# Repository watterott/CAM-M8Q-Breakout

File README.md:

# CAM-M8Q-Breakout
Breakout with u-blox CAM-M8Q Multi GNSS Module.

* [u-blox CAM-M8Q](https://www.u-blox.com/de/product/cam-m8-series) Multi GNSS Module
* GNSS Systems: GPS/QZSS, Galileo, GLONASS, BeiDou
* Interfaces: UART (default 9600 8N1), I2C/TWI (address 0x42), SPI
* on-board Antenna and optional external Antenna (u.Fl)
* 2.7 - 3.6V Power Supply
* Open-Source and released under the [Creative Commons Attribution Share-Alike License](https://creativecommons.org/licenses/by-sa/4.0/).
* **[Documentation on learn.watterott.com](https://learn.watterott.com)**

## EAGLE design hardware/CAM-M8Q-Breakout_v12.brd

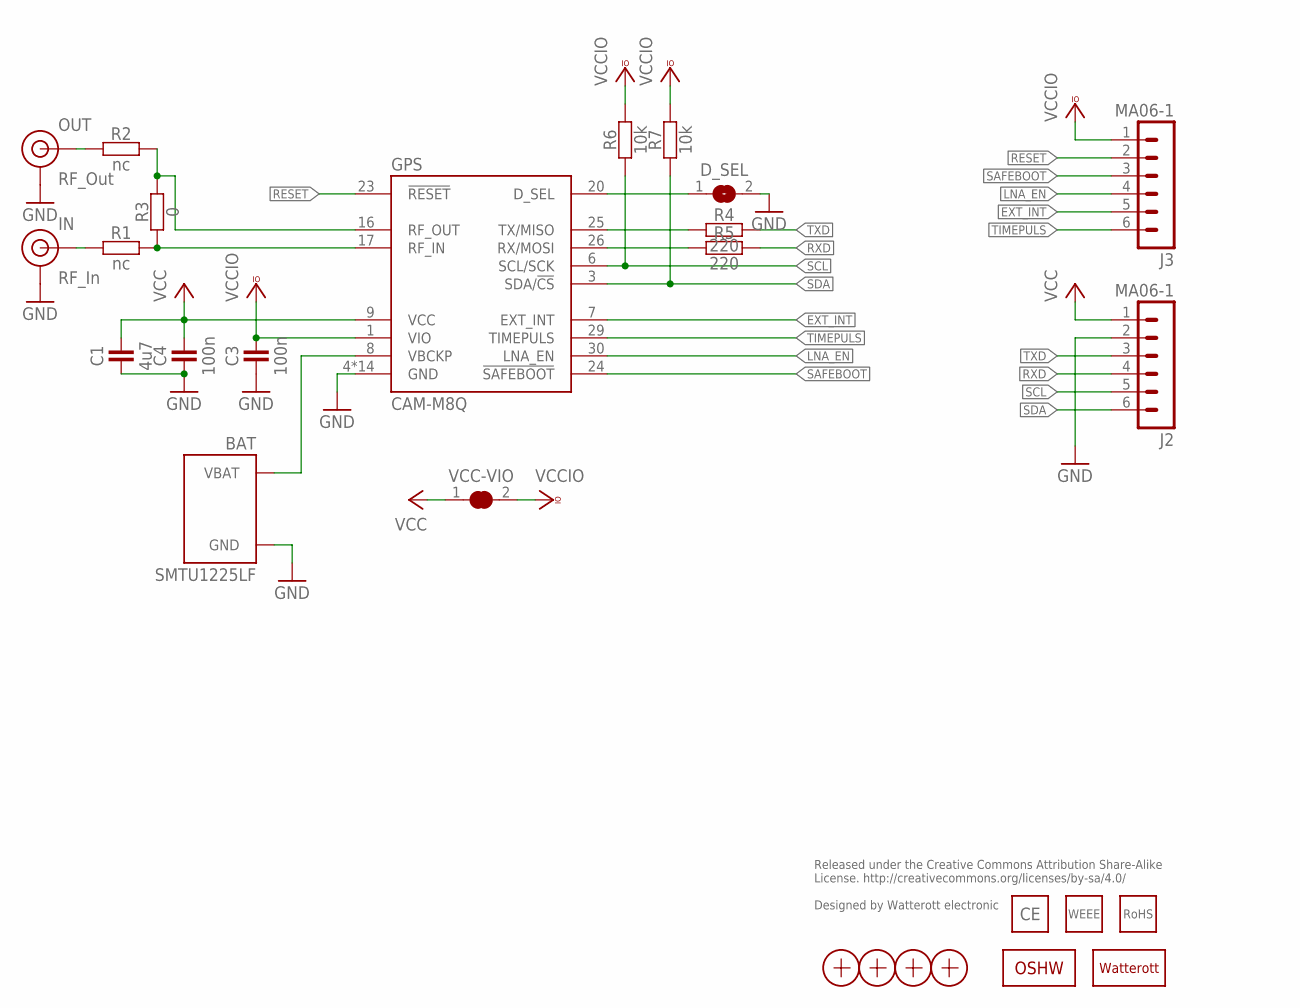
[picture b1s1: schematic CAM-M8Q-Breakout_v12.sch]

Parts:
BAT: SMTU1225LF; BAT-SMTU1225LF
C1: 4u7; C0402
C3, C4: 100n; C0402
D_SEL: JUMPER2-0603-NC; JUMPER2-0603_NC
GPS: CAM-M8Q
IN: RF_In; U.FL
J2, J3: MA06-1
LOGO1: LOGO-S_PLACE_M; SPARK_TPLACE_M
LOGO2: OSHW_LOGOX0070; OSHW_6X70
LOGO3: LOGO_CE-2; CE_2MM
LOGO4: LOGO_WEEE-4; WEEE_4MM
LOGO5: LOGO_ROHS-2; ROHS_2MM
OUT: RF_Out; U.FL
R1, R2: nc; C0402
R3: 0; C0402
R4, R5: 220; C0402
R6, R7: 10k; C0402
VCC-VIO: JUMPER2-0603-NC; JUMPER2-0603_NC
X1, X2, X3, X4: PASSER-07; PASSER_07MM

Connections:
D_SEL: D_SEL.1, GPS.20 (D_SEL)
EXT_INT: GPS.7 (EXT_INT), J3.5
GND: BAT.- (GND), C1.1, C3.1, C4.1, D_SEL.2, GPS.4 (GND), GPS.5 (GND), GPS.10 (GND), GPS.11 (GND), GPS.12 (GND), GPS.13 (GND), GPS.14 (GND), GPS.15 (GND), GPS.18 (GND), GPS.19 (GND), GPS.21 (GND), GPS.22 (GND), GPS.27 (GND), GPS.31 (GND), IN.1 (GND), IN.2 (GND), J2.2, OUT.1 (GND), OUT.2 (GND)
IN: IN.FEED (SIGNAL), R1.1
LNA_EN: GPS.30 (LNA_EN), J3.4
unnamed: GPS.25 (TX/MISO), R4.1
unnamed: GPS.26 (RX/MOSI), R5.1
OUT: OUT.FEED (SIGNAL), R2.1
RESET: GPS.23 (!RESET), J3.2
RFIN: GPS.17 (RF_IN), R1.2, R3.1
RFOUT: GPS.16 (RF_OUT), R2.2, R3.2
RXD: J2.4, R5.2
SAFEBOOT: GPS.24 (!SAFEBOOT), J3.3
SCL: GPS.6 (SCL/SCK), J2.5, R6.1
SDA: GPS.3 (SDA/!CS), J2.6, R7.1
TIMEPULS: GPS.29 (TIMEPULS), J3.6
TXD: J2.3, R4.2
VBCKP: BAT.+ (VBAT), GPS.8 (VBCKP)
VCC: C1.2, C4.2, GPS.9 (VCC), J2.1, VCC-VIO.1
VCCIO: C3.2, GPS.1 (VIO), J3.1, R6.2, R7.2, VCC-VIO.2

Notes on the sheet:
Released under the Creative Commons Attribution Share-Alike License. http://creativecommons.org/licenses/by-sa/4.0/ Designed by Watterott electronic

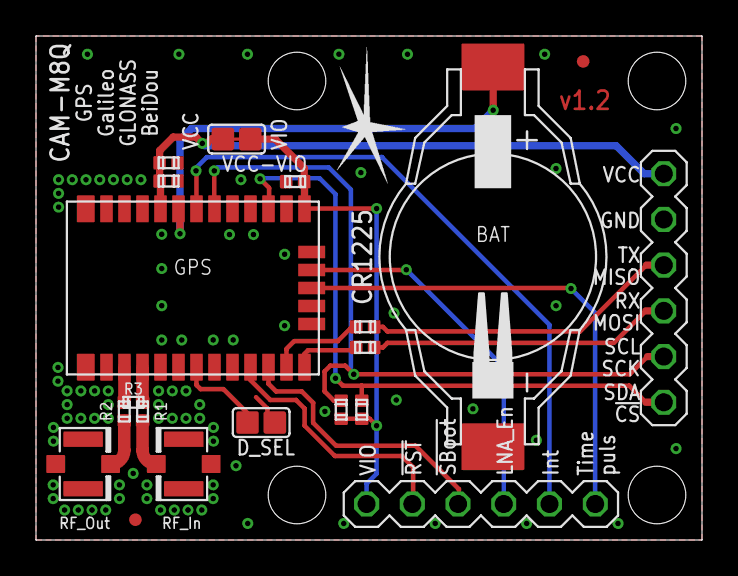
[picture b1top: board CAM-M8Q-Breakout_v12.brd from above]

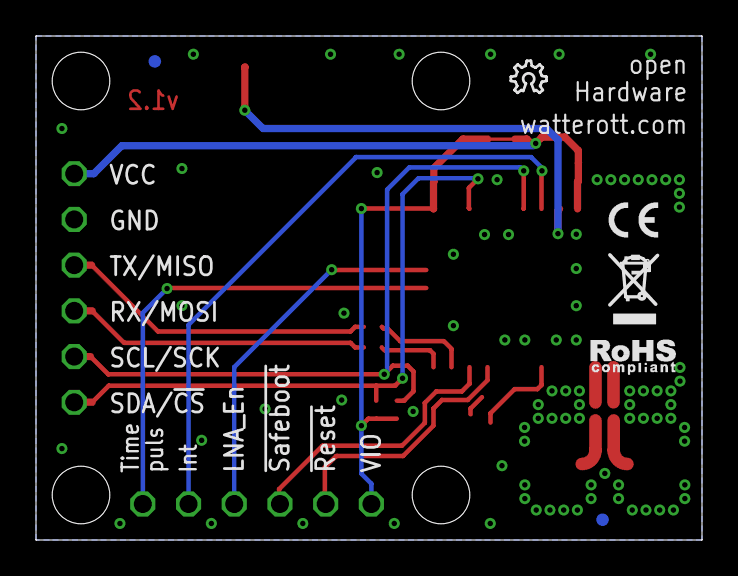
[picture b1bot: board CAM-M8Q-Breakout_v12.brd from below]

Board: 2 copper layers, 37.0 x 28.0 mm, 27 parts (6 on the bottom side), 20 nets.

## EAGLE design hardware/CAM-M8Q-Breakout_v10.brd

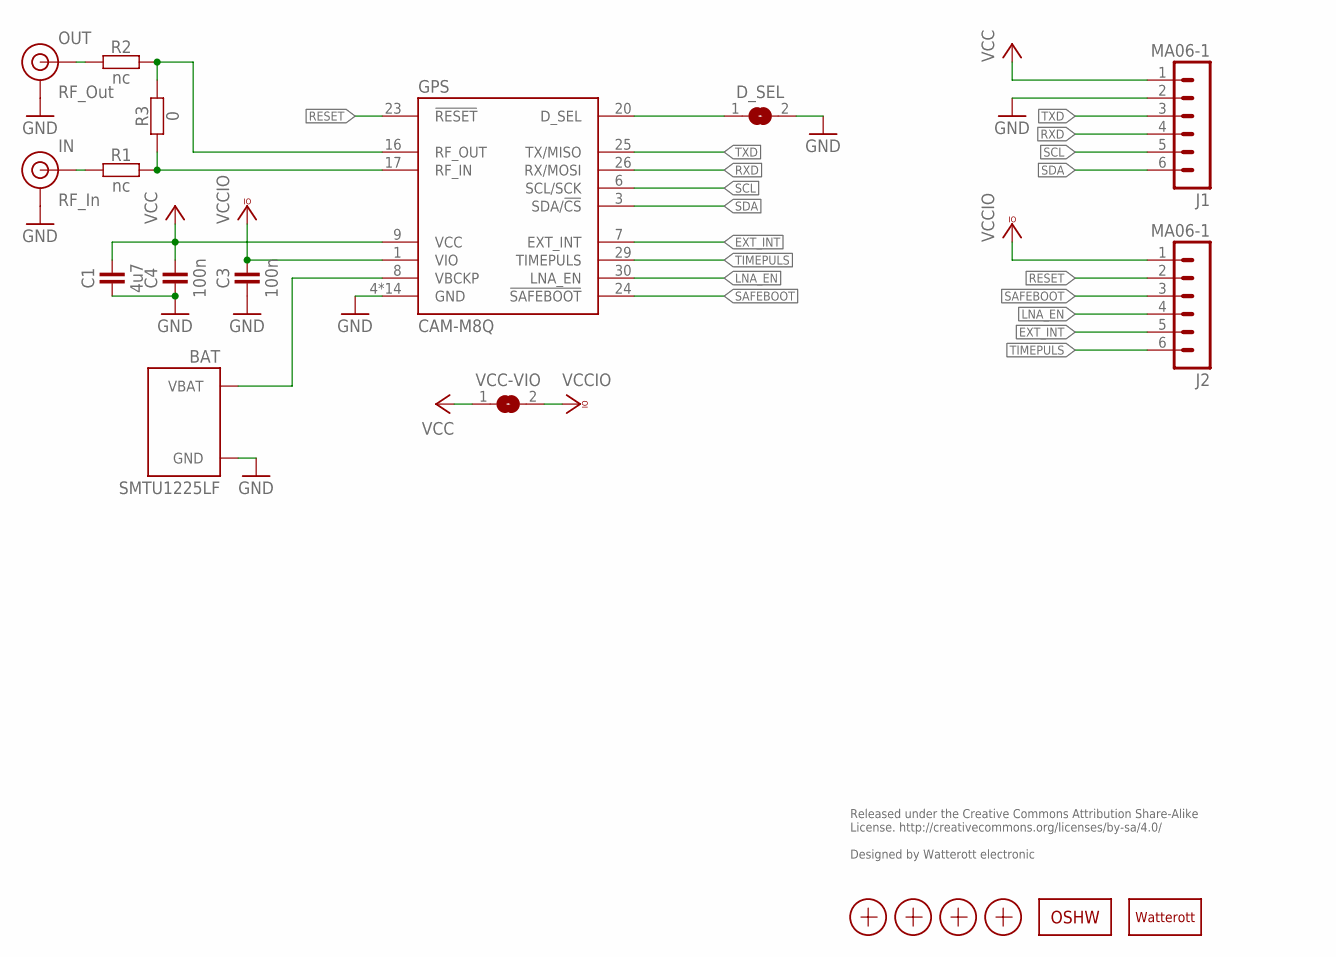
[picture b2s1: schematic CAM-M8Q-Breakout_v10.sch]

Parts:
BAT: SMTU1225LF; BAT-SMTU1225LF
C1: 4u7; C0402
C3, C4: 100n; C0402
D_SEL: JUMPER2-0603-NC; JUMPER2-0603_NC
GPS: CAM-M8Q
IN: RF_In; U.FL
J1, J2: MA06-1
LOGO1: LOGO-S_PLACE_M; SPARK_TPLACE_M
LOGO2: OSHW_LOGOX0070; OSHW_6X70
OUT: RF_Out; U.FL
R1, R2: nc; C0402
R3: 0; C0402
VCC-VIO: JUMPER2-0603-NC; JUMPER2-0603_NC
X1, X2, X3, X4: PASSER-07; PASSER_07MM

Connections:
D_SEL: D_SEL.1, GPS.20 (D_SEL)
EXT_INT: GPS.7 (EXT_INT), J2.5
GND: BAT.- (GND), C1.1, C3.1, C4.1, D_SEL.2, GPS.4 (GND), GPS.5 (GND), GPS.10 (GND), GPS.11 (GND), GPS.12 (GND), GPS.13 (GND), GPS.14 (GND), GPS.15 (GND), GPS.18 (GND), GPS.19 (GND), GPS.21 (GND), GPS.22 (GND), GPS.27 (GND), GPS.31 (GND), IN.1 (GND), IN.2 (GND), J1.2, OUT.1 (GND), OUT.2 (GND)
IN: IN.FEED (SIGNAL), R1.1
LNA_EN: GPS.30 (LNA_EN), J2.4
OUT: OUT.FEED (SIGNAL), R2.1
RESET: GPS.23 (!RESET), J2.2
RFIN: GPS.17 (RF_IN), R1.2, R3.1
RFOUT: GPS.16 (RF_OUT), R2.2, R3.2
RXD: GPS.26 (RX/MOSI), J1.4
SAFEBOOT: GPS.24 (!SAFEBOOT), J2.3
SCL: GPS.6 (SCL/SCK), J1.5
SDA: GPS.3 (SDA/!CS), J1.6
TIMEPULS: GPS.29 (TIMEPULS), J2.6
TXD: GPS.25 (TX/MISO), J1.3
VBCKP: BAT.+ (VBAT), GPS.8 (VBCKP)
VCC: C1.2, C4.2, GPS.9 (VCC), J1.1, VCC-VIO.1
VIO: C3.2, GPS.1 (VIO), J2.1, VCC-VIO.2

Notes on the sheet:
Released under the Creative Commons Attribution Share-Alike License. http://creativecommons.org/licenses/by-sa/4.0/ Designed by Watterott electronic

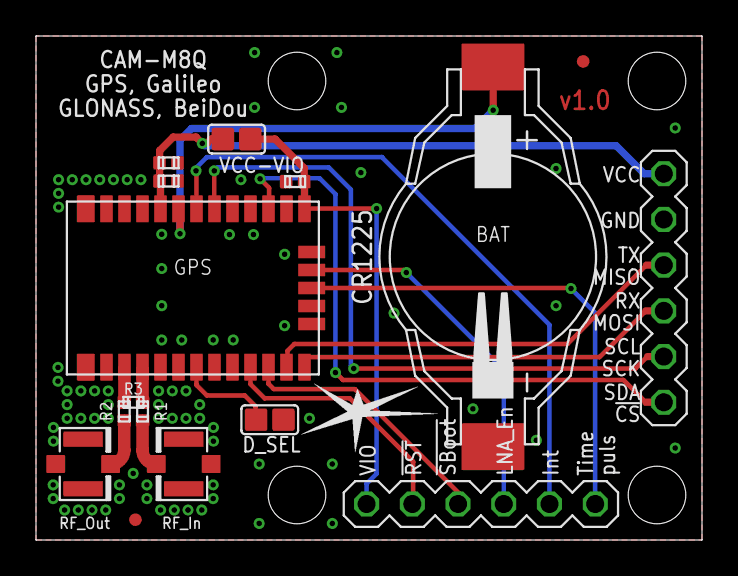
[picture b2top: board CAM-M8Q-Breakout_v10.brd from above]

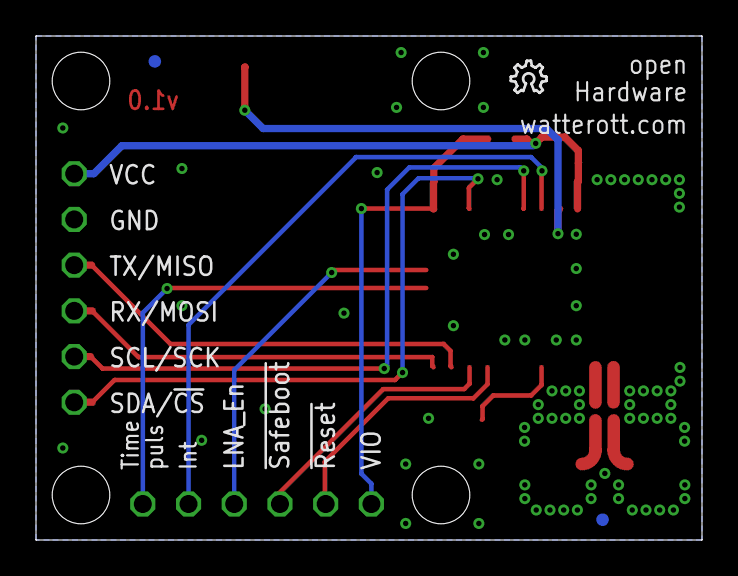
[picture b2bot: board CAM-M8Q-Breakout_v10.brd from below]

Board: 2 copper layers, 37.0 x 28.0 mm, 20 parts (3 on the bottom side), 18 nets.

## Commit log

2017-09-12 updated layout and schematics
2018-05-01 added rev 1.1
2018-08-09 updated schematics
2020-10-17 added V1.2
